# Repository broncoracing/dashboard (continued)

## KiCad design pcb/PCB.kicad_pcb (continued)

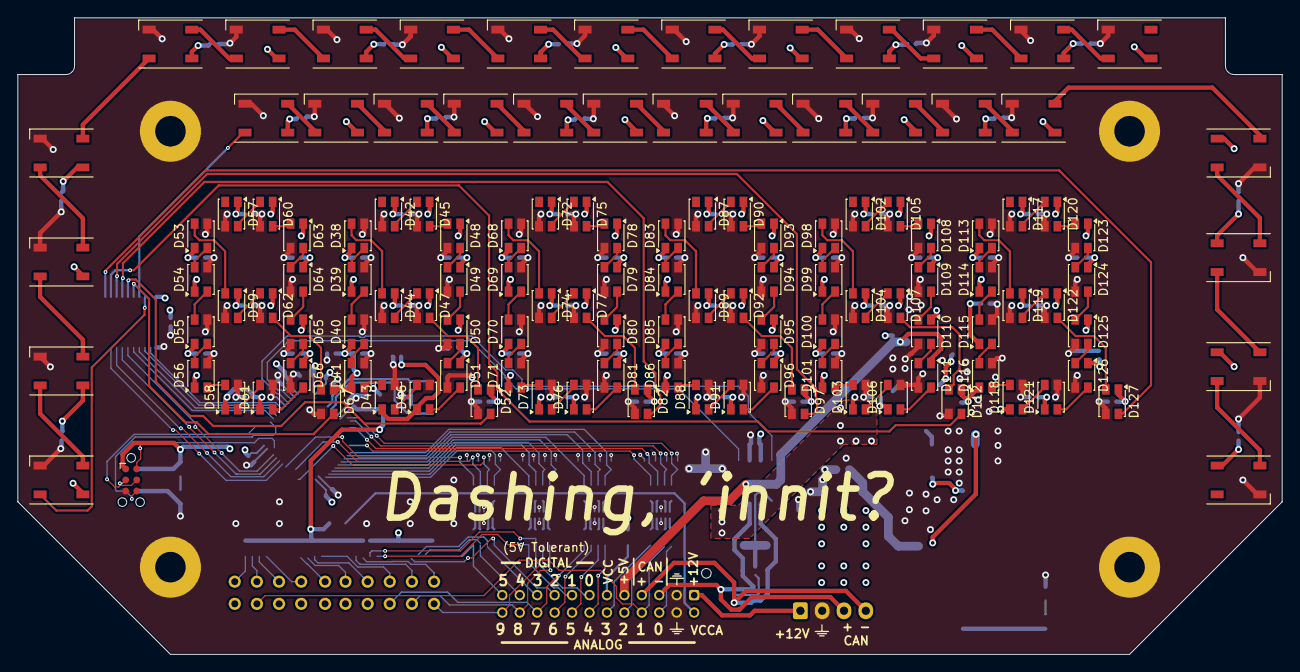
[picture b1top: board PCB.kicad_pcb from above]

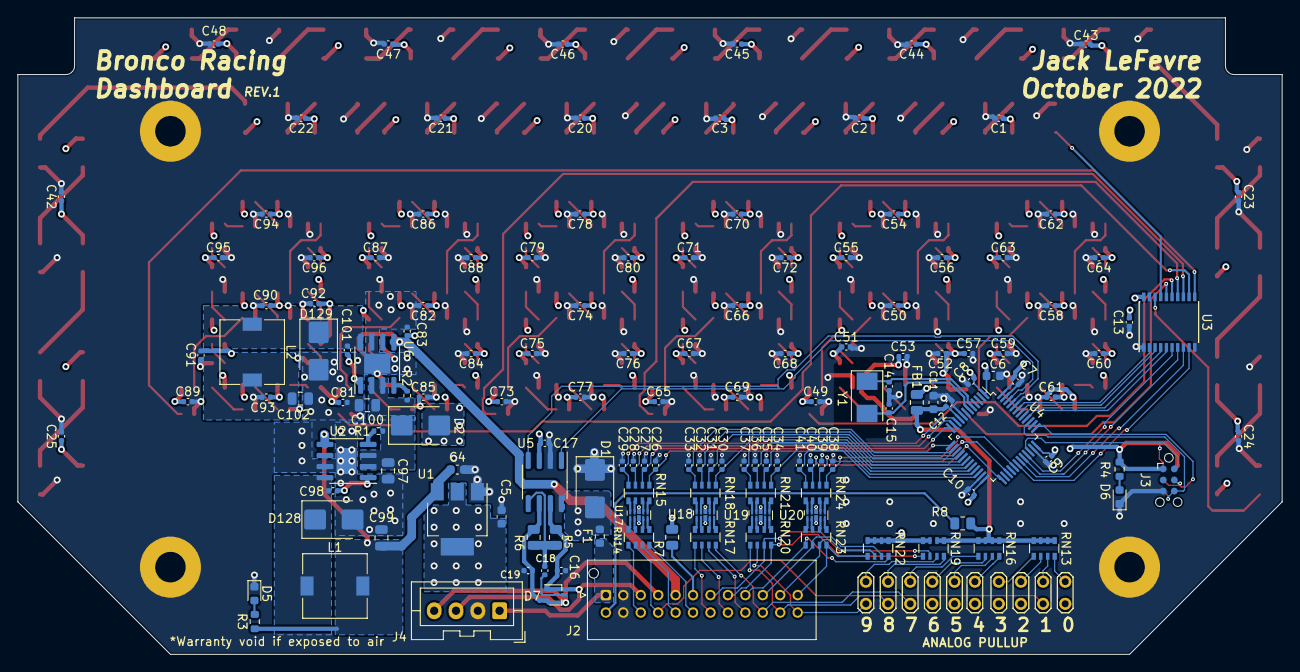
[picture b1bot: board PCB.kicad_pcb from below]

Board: 4 copper layers, 145.0 x 73.0 mm, 284 parts (157 on the bottom side), 233 nets.

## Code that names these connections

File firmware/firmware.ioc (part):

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Mcu.Name=STM32F103C(8-B)Tx
Mcu.Package=LQFP48
Mcu.UserName=STM32F103C8Tx
PA0-WKUP.Signal=ADCx_IN0
PA1.Signal=ADCx_IN1
PA10.GPIOParameters=GPIO_Speed,GPIO_Label
PA10.GPIO_Label=LED_6
PA10.GPIO_Speed=GPIO_SPEED_FREQ_HIGH
PA10.Signal=GPIO_Output
PA11.GPIOParameters=GPIO_Speed,GPIO_Label
PA11.GPIO_Label=LED_5
PA11.GPIO_Speed=GPIO_SPEED_FREQ_HIGH
PA11.Signal=GPIO_Output
PA12.GPIOParameters=GPIO_Speed,GPIO_Label
PA12.GPIO_Label=LED_4
PA12.GPIO_Speed=GPIO_SPEED_FREQ_HIGH
PA12.Signal=GPIO_Output
PA13.Mode=Trace_Asynchronous_SW
PA13.Signal=SYS_JTMS-SWDIO
PA14.Mode=Trace_Asynchronous_SW
PA14.Signal=SYS_JTCK-SWCLK
PA2.Signal=ADCx_IN2
PA3.Signal=ADCx_IN3
PA4.Signal=ADCx_IN4
PA5.Signal=ADCx_IN5
PA6.Signal=ADCx_IN6
PA7.Signal=ADCx_IN7
PA8.GPIOParameters=GPIO_Label
PA8.GPIO_Label=BTN5
PA8.Signal=GPIO_Input
PA9.GPIOParameters=GPIO_Speed,GPIO_Label
PA9.GPIO_Label=LED_7
PA9.GPIO_Speed=GPIO_SPEED_FREQ_HIGH
PA9.Signal=GPIO_Output
PB0.Signal=ADCx_IN8
PB1.Signal=ADCx_IN9
PB10.GPIOParameters=GPIO_Label
PB10.GPIO_Label=BTN1
PB10.Signal=GPIO_Input
PB11.GPIOParameters=GPIO_Label
PB11.GPIO_Label=BTN2
PB11.Signal=GPIO_Input
PB12.GPIOParameters=GPIO_Label
PB12.GPIO_Label=BTN3
PB12.Signal=GPIO_Input
PB14.GPIOParameters=GPIO_Label
PB14.GPIO_Label=BTN4
PB14.Signal=GPIO_Input
PB2.GPIOParameters=GPIO_Label
PB2.GPIO_Label=BTN0
PB2.Signal=GPIO_Input
PB3.Mode=Trace_Asynchronous_SW
PB3.Signal=SYS_JTDO-TRACESWO
PB4.GPIOParameters=GPIO_Speed,GPIO_Label
PB4.GPIO_Label=LED_3
PB4.GPIO_Speed=GPIO_SPEED_FREQ_HIGH
PB4.Signal=GPIO_Output
PB5.GPIOParameters=GPIO_Speed,GPIO_Label
PB5.GPIO_Label=LED_2
PB5.GPIO_Speed=GPIO_SPEED_FREQ_HIGH
PB5.Signal=GPIO_Output
PB6.GPIOParameters=GPIO_Speed,GPIO_Label
PB6.GPIO_Label=LED_1
PB6.GPIO_Speed=GPIO_SPEED_FREQ_HIGH
PB6.Signal=GPIO_Output
PB7.GPIOParameters=GPIO_Speed,GPIO_Label
PB7.GPIO_Label=LED_0
PB7.GPIO_Speed=GPIO_SPEED_FREQ_HIGH
PB7.Signal=GPIO_Output
PB8.GPIOParameters=GPIO_PuPd,GPIO_Mode
PB8.GPIO_Mode=GPIO_MODE_INPUT
PB8.GPIO_PuPd=GPIO_NOPULL
PB8.Mode=CAN_Activate
PB8.Signal=CAN_RX
PB9.Mode=CAN_Activate
PB9.Signal=CAN_TX
PD0-OSC_IN.Mode=HSE-External-Oscillator
PD0-OSC_IN.Signal=RCC_OSC_IN
PD1-OSC_OUT.Mode=HSE-External-Oscillator
PD1-OSC_OUT.Signal=RCC_OSC_OUT
RCC.SYSCLKFreq_VALUE=128000000
RCC.SYSCLKSource=RCC_SYSCLKSOURCE_PLLCLK
board=custom

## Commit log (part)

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2022-09-29 Create schematic
2022-09-30 Laid out and routed PCB
2022-09-30 fix github workflow path
2022-09-30 re-fix github workflow :(
2022-10-02 Added debug/test header
2022-10-03 Added silkscreen markings
2022-11-21 Fixed DRC violations
2023-01-17 Added 5v output on main connector, labeled 5v tolerant pins
2023-01-23 De-borked symbol library for segment displays
2023-01-29 Changes from design review
2023-01-29 Added firmware project structure and testing firmware
2023-01-29 Added part numbers for assembly
2023-01-31 Started work on discrete led displays
2023-01-31 PCB layout work
2023-01-31 Finished layout
2023-02-01 bottom text
2023-02-06 Use Neopixels for segment displays (#2)
    * Create schematic
    * Laid out and routed PCB
    * fix github workflow path
    * re-fix github workflow :(
    * Added debug/test header
    * Added silkscreen markings
2023-02-23 Started work on FW for neopixel version
2023-02-24 Disconnected NRESET
2023-03-03 Firmware work
2023-03-03 Added dial input on ADC0/1
2023-03-03 Added CAN reading
2023-03-03 Send dials over CAN to ecu
2023-03-17 Switch to DMA for WS2812 control
2023-03-26 Fix PCB, use DMA for ws2812 LEDs (#5)
    * Disconnected NRESET
    * Firmware work
    * Added dial input on ADC0/1
    * Added CAN reading
    * Send dials over CAN to ecu
    * Switch to DMA for WS2812 control
2023-03-26 make it work with bootloader
2023-04-03 Tried to fix kibot render
    :)
2023-04-04 Work on dash UI and refactoring
2023-04-04 Changed like everything lol
2023-04-04 Updated can-ids, UI for engine running/off
2023-04-10 Add dyno mode and first attempt at fixing northern lights
2023-05-01 update can IDs
2023-05-06 Overclock microcontroller to try to fix flickers
2023-05-06 fix ws2812 timings
2023-05-06 tweak timings for ws2812s
2023-05-06 still trying to fix flickers
2023-05-06 stiiiiil trying
2023-05-06 sigh
2023-05-06 shotgun debugging
2023-05-06 fixed northern lights
2023-05-15 fixe buttonss
2023-08-31 Updated CAN IDs
2023-09-01 changes for diag mode and stuff
2023-09-01 Update UI
2023-11-12 change to kicad 7, fix led signal direction for segment displays
2023-11-13 Update kibot.yml to kicad 7
2023-11-13 Fix kikad 7 schematic issues
2023-11-13 why drc broken
2023-11-13 update kicad library
2023-11-13 update ws2812 library footprint
2024-03-04 small ui fixes
2024-03-04 fix gitignore
2024-03-04 update can-ids
2025-05-10 BR25 Dashboard
2025-05-10 added br24 changes
2025-05-10 Parts
2025-05-10 LED Footprints fixed
2025-06-18 jlink debugging and fixed pointer error
2025-12-01 Update startup animation to say BR-26
    Currently the startup animation said BR-23, I changed it to say BR-26.
2025-12-19 Add to CAN IDs submodule and dashboard UI firmware changes
